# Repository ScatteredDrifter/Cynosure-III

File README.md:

# Cynosure-III
A 38-Key split-keyboard based on Xiao-rp2040 seeduino

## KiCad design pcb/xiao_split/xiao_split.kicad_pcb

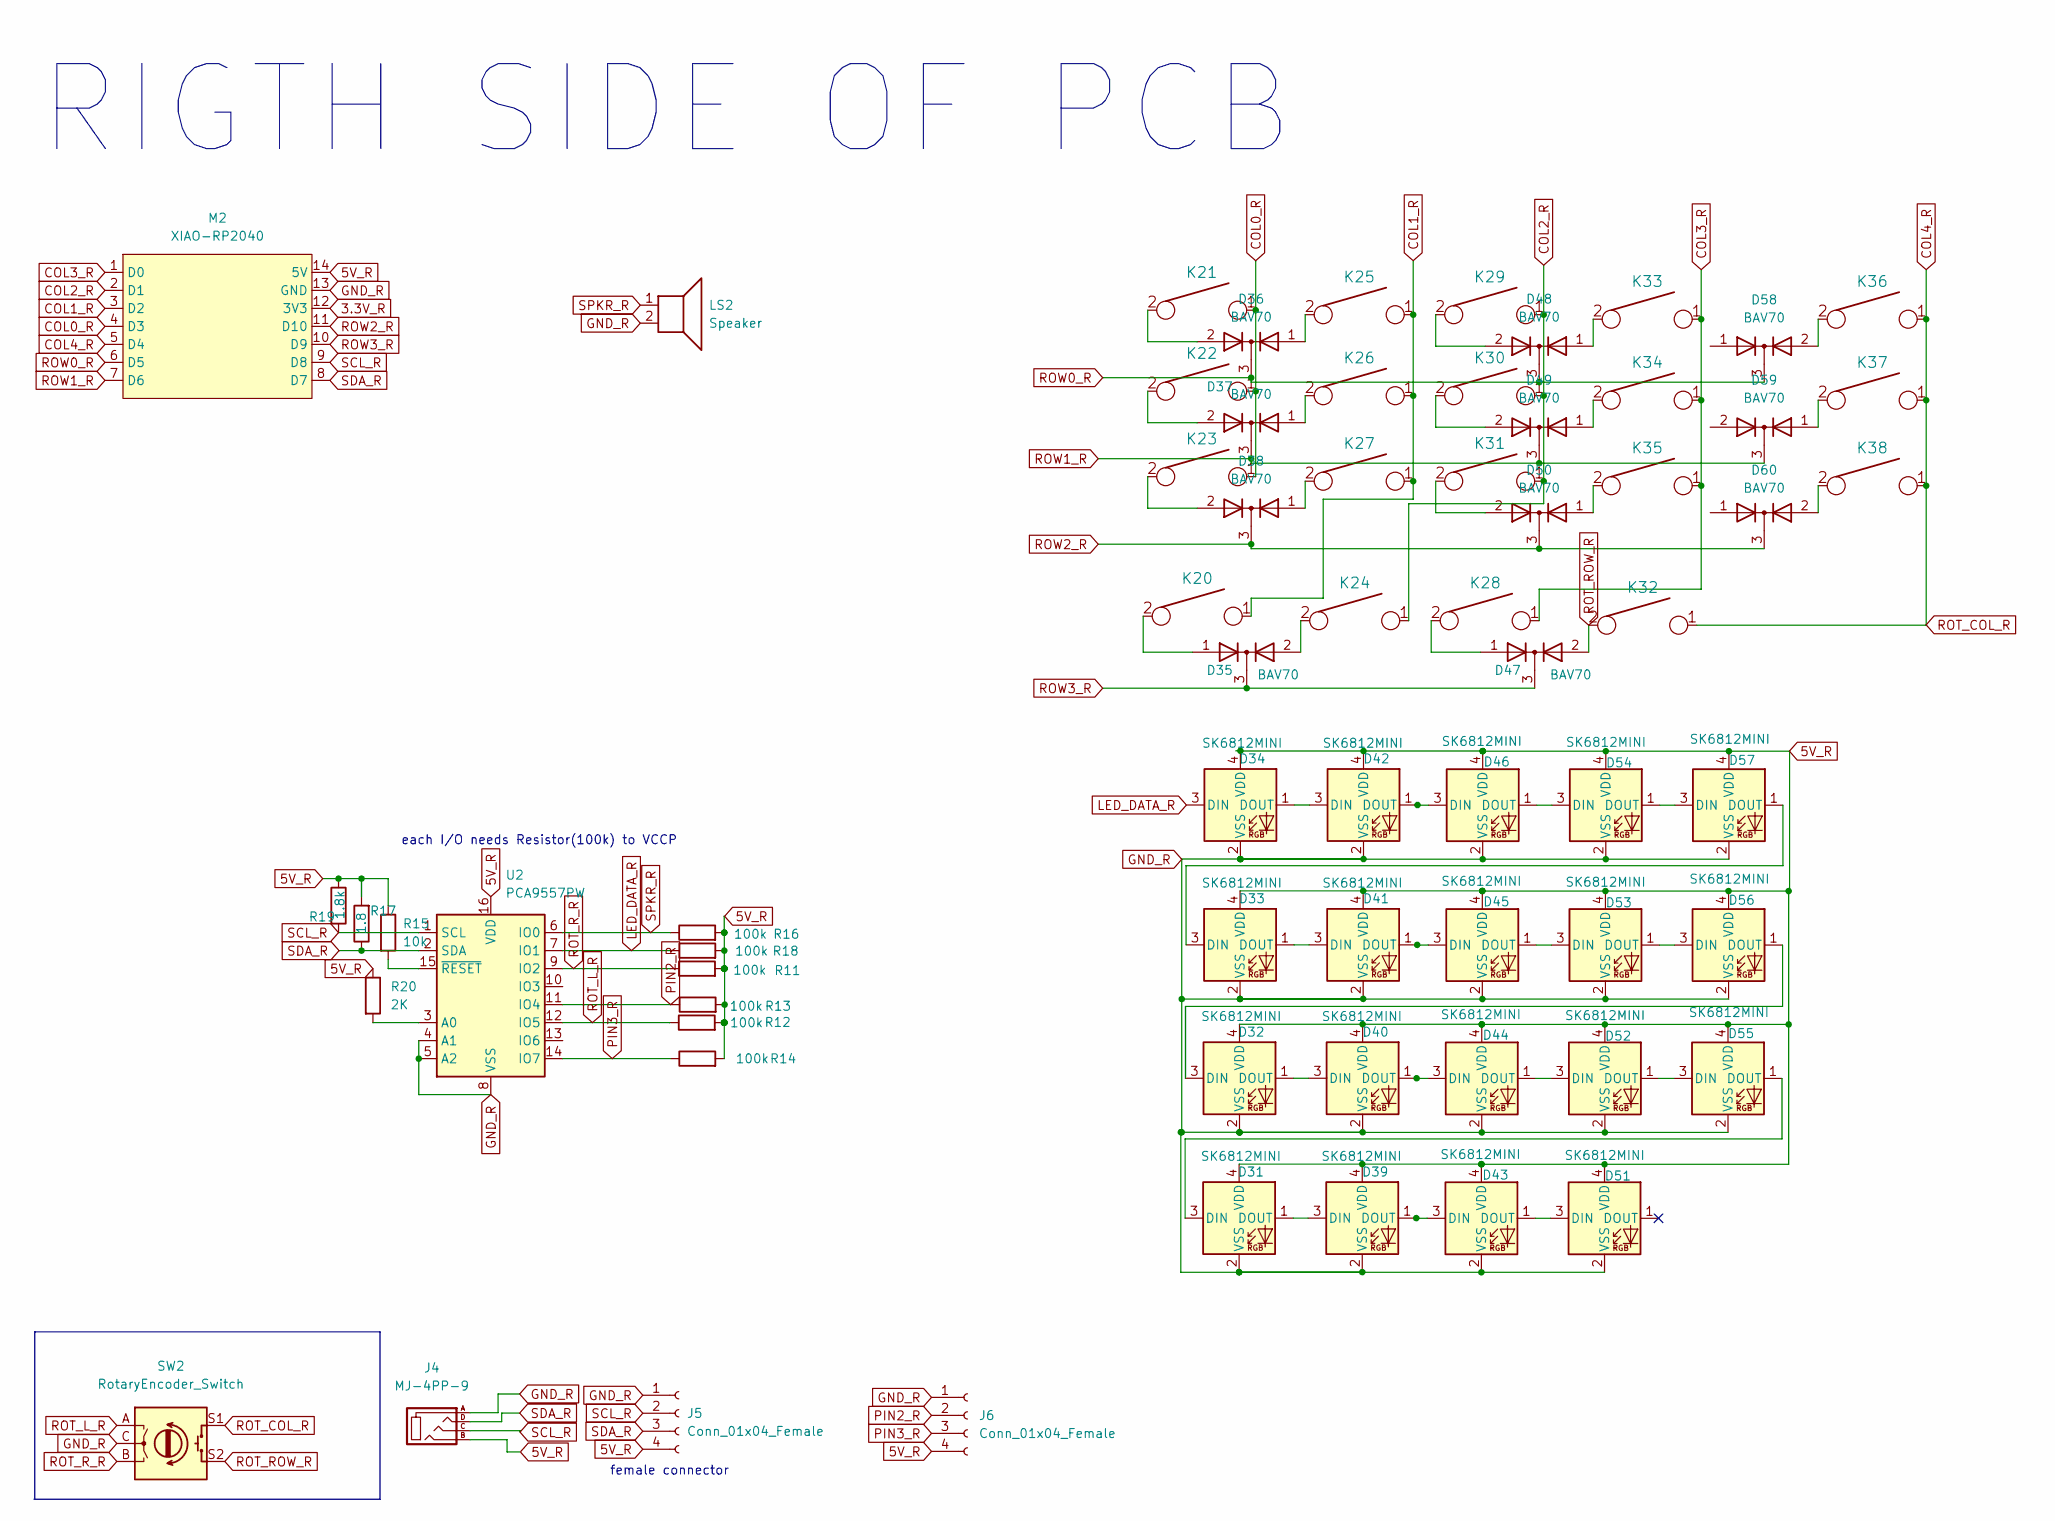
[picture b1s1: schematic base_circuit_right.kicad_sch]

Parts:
D31, D32, D33, D34, D39, D40, D41, D42, D43, D44, D45, D46, D51, D52, D53, D54, D55, D56, D57: SK6812MINI; SK6812-MINI-E; MPN SK6812MINI
D35, D36, D37, D38, D47, D48, D49, D50, D58, D59, D60: BAV70; SOT-23; MPN BAV70
J4: MJ-4PP-9; TRRS-PJ-320A; MPN PJ-3200B-4A
J5: Conn_01x04_Female; PinSocket_1x06_P2.54mm_Vertical
J6: Conn_01x04_Female; PinSocket_1x04_P2.00mm_Vertical
K20, K21, K22, K23, K24, K25, K26, K27, K28, K29, K30, K31, K32, K33, K34, K35, K36, K37, K38: KEYSW; MX-Alps-Choc-1U-NoLED; MPN 1350
LS2: Speaker; AST1109MLTRQ
M2: XIAO-RP2040; xiao-tht; MPN XIAO RP2040
R11, R12, R13, R14, R16, R18: 100k; R_0805_2012Metric; MPN RC0805FR-07100KL
R15: 10k; R_0805_2012Metric; MPN RC0805FR-0710KL
R17: 1.8; R_0805_2012Metric; MPN RC0805FR-071K8L
R19: 1.8k; R_0805_2012Metric; MPN RC0805FR-071K8L
R20: 2K; R_0805_2012Metric; MPN RC0805JR-072KL
SW2: RotaryEncoder_Switch; RotaryEncoder_EC11; MPN EC11E183440C
U2: PCA9557PW; TSSOP-16_4.4x5mm_P0.65mm

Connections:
3.3V_R: M2.12 (3V3)
5V_R: D31.4 (VDD), D32.4 (VDD), D33.4 (VDD), D34.4 (VDD), D39.4 (VDD), D40.4 (VDD), D41.4 (VDD), D42.4 (VDD), D43.4 (VDD), D44.4 (VDD), D45.4 (VDD), D46.4 (VDD), D51.4 (VDD), D52.4 (VDD), D53.4 (VDD), D54.4 (VDD), D55.4 (VDD), D56.4 (VDD), D57.4 (VDD), J4.B, J5.4, J6.4, M2.14 (5V), R11.2, R12.2, R13.2, R14.2, R15.1, R16.2, R17.2, R18.2, R19.1, R20.1, U2.16 (VDD)
COL0_R: K21.1, K22.1, K23.1, M2.4 (D3)
COL1_R: K20.1, K25.1, K26.1, K27.1, M2.3 (D2)
COL2_R: K24.1, K29.1, K30.1, K31.1, M2.2 (D1)
COL3_R: K28.1, K33.1, K34.1, K35.1, M2.1 (D0)
COL4_R: K32.1, K36.1, K37.1, K38.1, M2.5 (D4), SW2.S1
GND_R: D31.2 (VSS), D32.2 (VSS), D33.2 (VSS), D34.2 (VSS), D39.2 (VSS), D40.2 (VSS), D41.2 (VSS), D42.2 (VSS), D43.2 (VSS), D44.2 (VSS), D45.2 (VSS), D46.2 (VSS), D51.2 (VSS), D52.2 (VSS), D53.2 (VSS), D54.2 (VSS), D55.2 (VSS), D56.2 (VSS), D57.2 (VSS), J4.A, J5.1, J6.1, LS2.2, M2.13 (GND), SW2.C, U2.4 (A1), U2.5 (A2), U2.8 (VSS)
LED_DATA_R: D34.3 (DIN), R18.1, U2.7 (IO1)
unnamed: D31.1 (DOUT), D39.3 (DIN)
unnamed: D31.3 (DIN), D55.1 (DOUT)
unnamed: D32.1 (DOUT), D40.3 (DIN)
unnamed: D32.3 (DIN), D56.1 (DOUT)
unnamed: D33.1 (DOUT), D41.3 (DIN)
unnamed: D33.3 (DIN), D57.1 (DOUT)
unnamed: D34.1 (DOUT), D42.3 (DIN)
unnamed: D35.1 (A), K20.2
unnamed: D35.2 (A), K24.2
unnamed: D36.1 (A), K25.2
unnamed: D36.2 (A), K21.2
unnamed: D37.1 (A), K26.2
unnamed: D37.2 (A), K22.2
unnamed: D38.1 (A), K27.2
unnamed: D38.2 (A), K23.2
unnamed: D39.1 (DOUT), D43.3 (DIN)
unnamed: D40.1 (DOUT), D44.3 (DIN)
unnamed: D41.1 (DOUT), D45.3 (DIN)
unnamed: D42.1 (DOUT), D46.3 (DIN)
unnamed: D43.1 (DOUT), D51.3 (DIN)
unnamed: D44.1 (DOUT), D52.3 (DIN)
unnamed: D45.1 (DOUT), D53.3 (DIN)
unnamed: D46.1 (DOUT), D54.3 (DIN)
unnamed: D47.1 (A), K28.2
unnamed: D48.1 (A), K33.2
unnamed: D48.2 (A), K29.2
unnamed: D49.1 (A), K34.2
unnamed: D49.2 (A), K30.2
unnamed: D50.1 (A), K35.2
unnamed: D50.2 (A), K31.2
unnamed: D52.1 (DOUT), D55.3 (DIN)
unnamed: D53.1 (DOUT), D56.3 (DIN)
unnamed: D54.1 (DOUT), D57.3 (DIN)
unnamed: D58.2 (A), K36.2
unnamed: D59.1 (A), K37.2
unnamed: D60.2 (A), K38.2
unnamed: R20.2, U2.3 (A0)
unnamed: R15.2, U2.15 (~RESET)
PIN2_R: J6.2, R13.1, U2.11 (IO4)
PIN3_R: J6.3, R14.1, U2.14 (IO7)
ROT_L_R: R12.1, SW2.A, U2.12 (IO5)
ROT_ROW_R: D47.2 (A), K32.2, SW2.S2
ROT_R_R: R11.1, SW2.B, U2.9 (IO2)
ROW0_R: D36.3 (K), D48.3 (K), D58.3 (K), M2.6 (D5)
ROW1_R: D37.3 (K), D49.3 (K), D59.3 (K), M2.7 (D6)
ROW2_R: D38.3 (K), D50.3 (K), D60.3 (K), M2.11 (D10)
ROW3_R: D35.3 (K), D47.3 (K), M2.10 (D9)
SCL_R: J4.C, J5.2, M2.9 (D8), R19.2, U2.1 (SCL)
SDA_R: J4.D, J5.3, M2.8 (D7), R17.1, U2.2 (SDA)
SPKR_R: LS2.1, R16.1, U2.6 (IO0)

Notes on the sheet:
each I/O needs Resistor(100k) to VCCP
RIGTH SIDE OF PCB
female connector

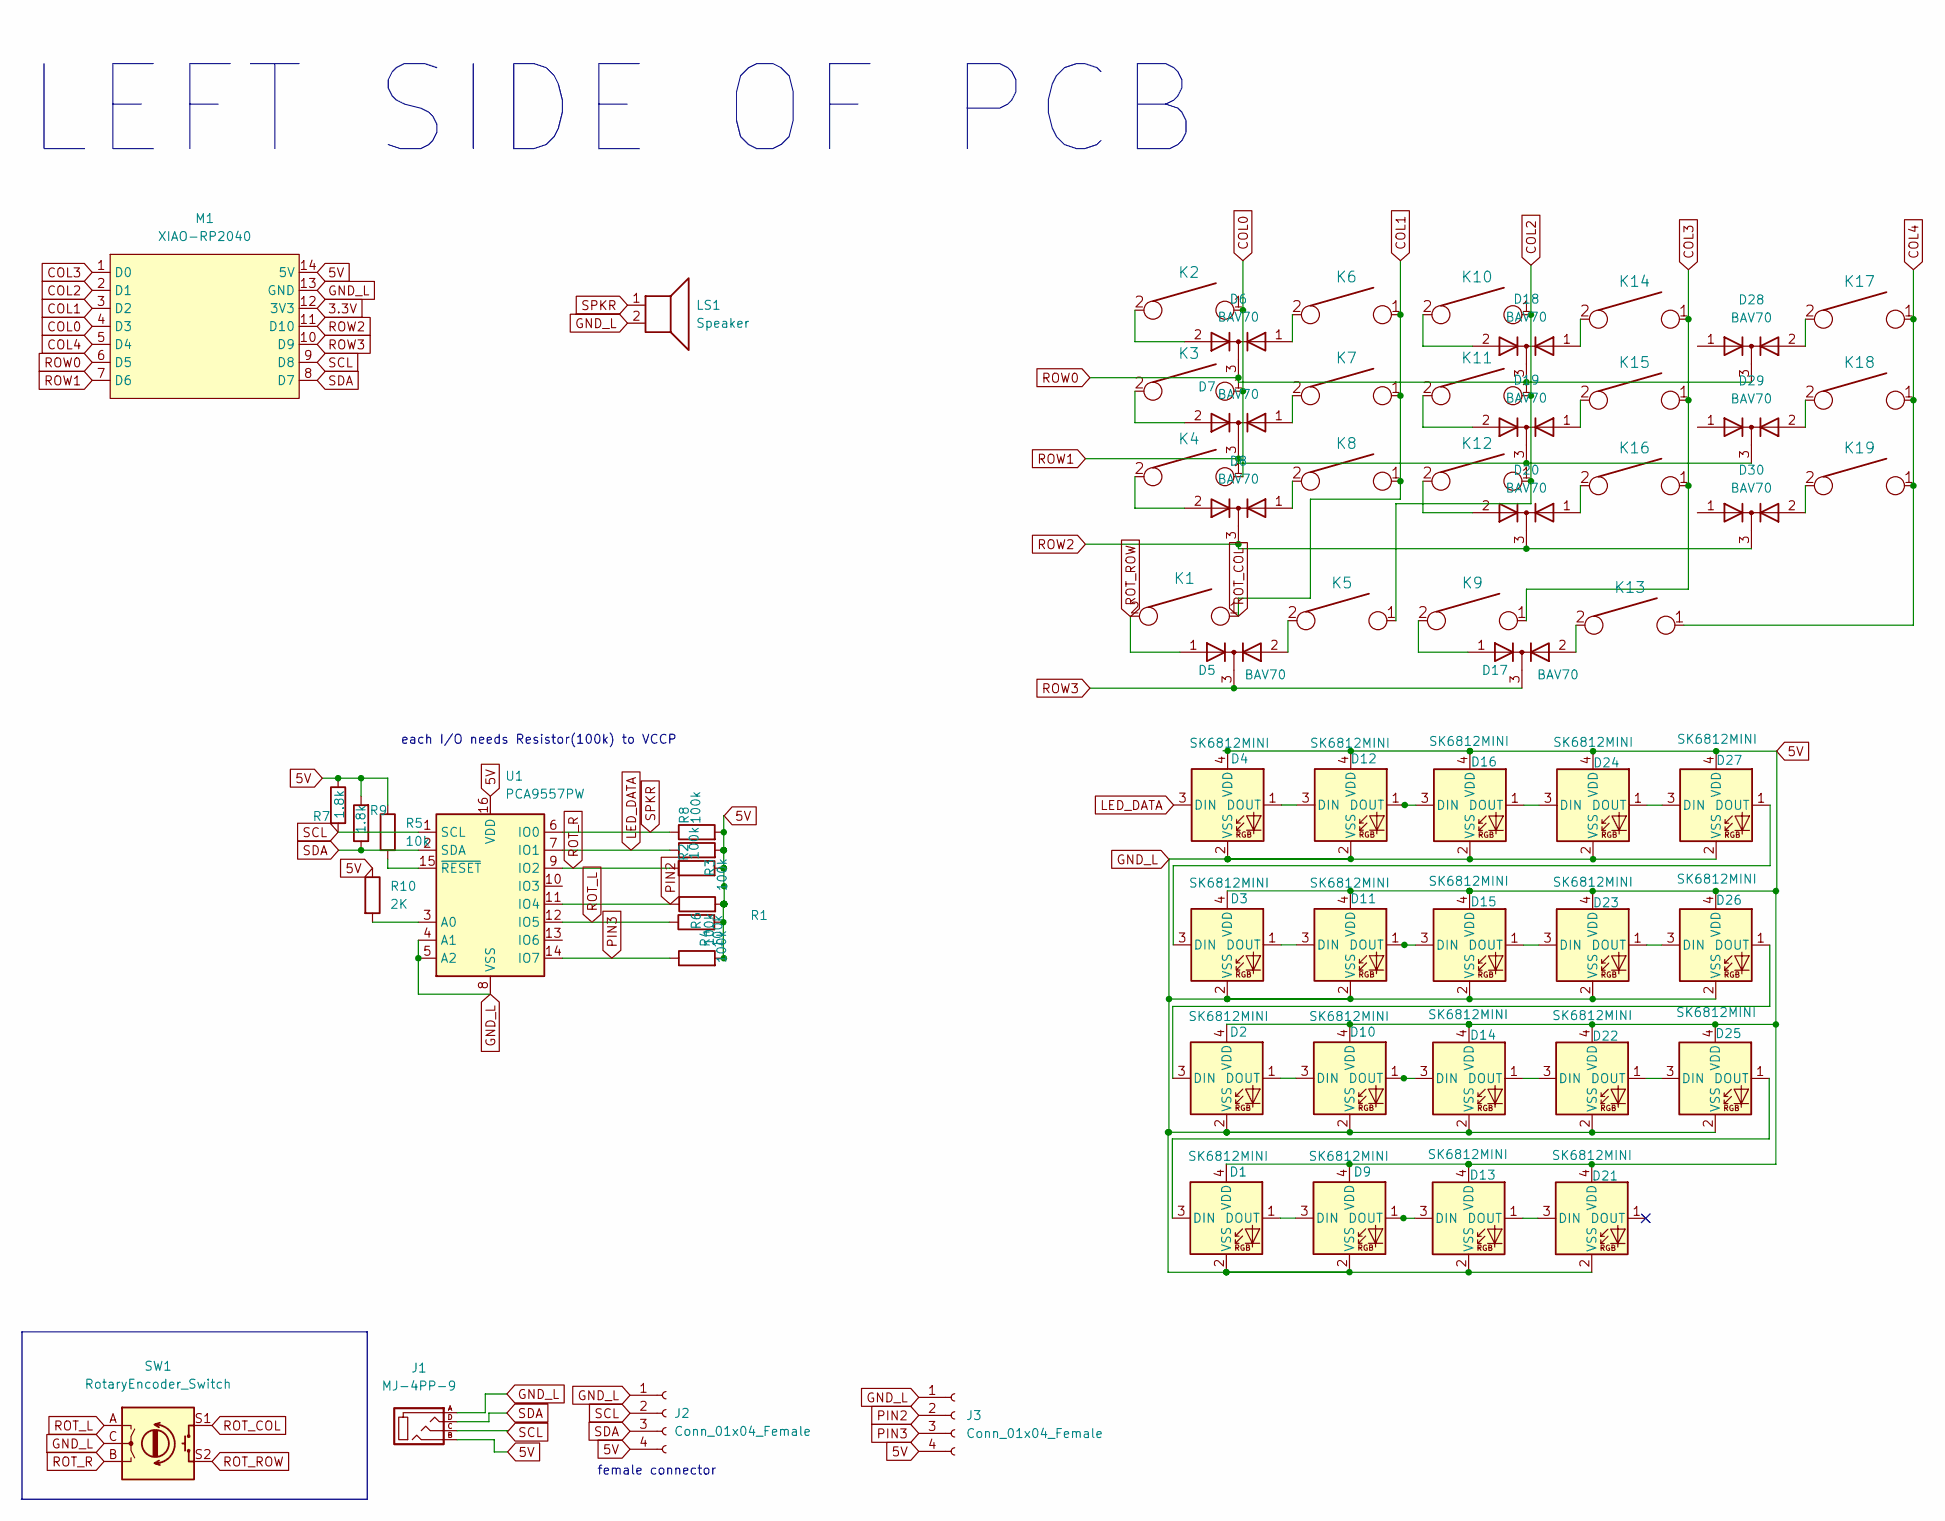
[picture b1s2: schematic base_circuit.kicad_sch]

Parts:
D1, D2, D3, D4, D9, D10, D11, D12, D13, D14, D15, D16, D21, D22, D23, D24, D25, D26, D27: SK6812MINI; SK6812-MINI-E; MPN SK6812MINI
D5, D6, D7, D8, D17, D18, D19, D20, D28, D29, D30: BAV70; SOT-23; MPN BAV70
J1: MJ-4PP-9; TRRS-PJ-320A; MPN PJ-3200B-4A
J2: Conn_01x04_Female; PinSocket_1x06_P2.54mm_Vertical
J3: Conn_01x04_Female; PinSocket_1x04_P2.00mm_Vertical
K1, K2, K3, K4, K5, K6, K7, K8, K9, K10, K11, K12, K13, K14, K15, K16, K17, K18, K19: KEYSW; MX-Alps-Choc-1U-NoLED; MPN 1350
LS1: Speaker; AST1109MLTRQ
M1: XIAO-RP2040; xiao-tht; MPN XIAO RP2040
R1, R2, R3, R4, R6, R8: 100k; R_0805_2012Metric; MPN RC0805FR-07100KL
R5: 10k; R_0805_2012Metric; MPN RC0805FR-0710KL
R7, R9: 1.8k; R_0805_2012Metric; MPN RC0805FR-071K8L
R10: 2K; R_0805_2012Metric; MPN RC0805JR-072KL
SW1: RotaryEncoder_Switch; RotaryEncoder_EC11; MPN EC11E183440C
U1: PCA9557PW; TSSOP-16_4.4x5mm_P0.65mm

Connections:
3.3V: M1.12 (3V3)
5V: D1.4 (VDD), D2.4 (VDD), D3.4 (VDD), D4.4 (VDD), D9.4 (VDD), D10.4 (VDD), D11.4 (VDD), D12.4 (VDD), D13.4 (VDD), D14.4 (VDD), D15.4 (VDD), D16.4 (VDD), D21.4 (VDD), D22.4 (VDD), D23.4 (VDD), D24.4 (VDD), D25.4 (VDD), D26.4 (VDD), D27.4 (VDD), J1.B, J2.4, J3.4, M1.14 (5V), R1.2, R4.2, R5.1, R6.2, R7.1, R8.2, R9.2, R10.1, U1.16 (VDD)
COL0: K2.1, K3.1, K4.1, M1.4 (D3)
COL1: K1.1, K6.1, K7.1, K8.1, M1.3 (D2), SW1.S1
COL2: K5.1, K10.1, K11.1, K12.1, M1.2 (D1)
COL3: K9.1, K14.1, K15.1, K16.1, M1.1 (D0)
COL4: K13.1, K17.1, K18.1, K19.1, M1.5 (D4)
GND_L: D1.2 (VSS), D2.2 (VSS), D3.2 (VSS), D4.2 (VSS), D9.2 (VSS), D10.2 (VSS), D11.2 (VSS), D12.2 (VSS), D13.2 (VSS), D14.2 (VSS), D15.2 (VSS), D16.2 (VSS), D21.2 (VSS), D22.2 (VSS), D23.2 (VSS), D24.2 (VSS), D25.2 (VSS), D26.2 (VSS), D27.2 (VSS), J1.A, J2.1, J3.1, LS1.2, M1.13 (GND), SW1.C, U1.4 (A1), U1.5 (A2), U1.8 (VSS)
LED_DATA: D4.3 (DIN), R3.1, U1.7 (IO1)
unnamed: D1.1 (DOUT), D9.3 (DIN)
unnamed: D1.3 (DIN), D25.1 (DOUT)
unnamed: D2.3 (DIN), D26.1 (DOUT)
unnamed: D5.2 (A), K5.2
unnamed: D6.1 (A), K6.2
unnamed: D6.2 (A), K2.2
unnamed: D7.1 (A), K7.2
unnamed: D7.2 (A), K3.2
unnamed: D8.1 (A), K8.2
unnamed: D8.2 (A), K4.2
unnamed: D10.1 (DOUT), D14.3 (DIN)
unnamed: D2.1 (DOUT), D10.3 (DIN)
unnamed: D11.1 (DOUT), D15.3 (DIN)
unnamed: D3.1 (DOUT), D11.3 (DIN)
unnamed: D12.1 (DOUT), D16.3 (DIN)
unnamed: D4.1 (DOUT), D12.3 (DIN)
unnamed: D13.1 (DOUT), D21.3 (DIN)
unnamed: D9.1 (DOUT), D13.3 (DIN)
unnamed: D14.1 (DOUT), D22.3 (DIN)
unnamed: D15.1 (DOUT), D23.3 (DIN)
unnamed: D16.1 (DOUT), D24.3 (DIN)
unnamed: D17.1 (A), K9.2
unnamed: D17.2 (A), K13.2
unnamed: D18.1 (A), K14.2
unnamed: D18.2 (A), K10.2
unnamed: D19.1 (A), K15.2
unnamed: D19.2 (A), K11.2
unnamed: D20.1 (A), K16.2
unnamed: D20.2 (A), K12.2
unnamed: D22.1 (DOUT), D25.3 (DIN)
unnamed: D23.1 (DOUT), D26.3 (DIN)
unnamed: D24.1 (DOUT), D27.3 (DIN)
unnamed: D3.3 (DIN), D27.1 (DOUT)
unnamed: D28.2 (A), K17.2
unnamed: D29.2 (A), K18.2
unnamed: D30.2 (A), K19.2
unnamed: R5.2, U1.15 (~RESET)
unnamed: R10.2, U1.3 (A0)
PIN2: J3.2, R6.1, U1.11 (IO4)
PIN3: J3.3, R4.1, U1.14 (IO7)
ROT_L: R1.1, SW1.A, U1.12 (IO5)
ROT_R: R2.1, SW1.B, U1.9 (IO2)
ROT_ROW: D5.1 (A), K1.2, SW1.S2
ROW0: D6.3 (K), D18.3 (K), D28.3 (K), M1.6 (D5)
ROW1: D7.3 (K), D19.3 (K), D29.3 (K), M1.7 (D6)
ROW2: D8.3 (K), D20.3 (K), D30.3 (K), M1.11 (D10)
ROW3: D5.3 (K), D17.3 (K), M1.10 (D9)
SCL: J1.C, J2.2, M1.9 (D8), R7.2, U1.1 (SCL)
SDA: J1.D, J2.3, M1.8 (D7), R9.1, U1.2 (SDA)
SPKR: LS1.1, R8.1, U1.6 (IO0)

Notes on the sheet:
each I/O needs Resistor(100k) to VCCP
LEFT SIDE OF PCB
female connector

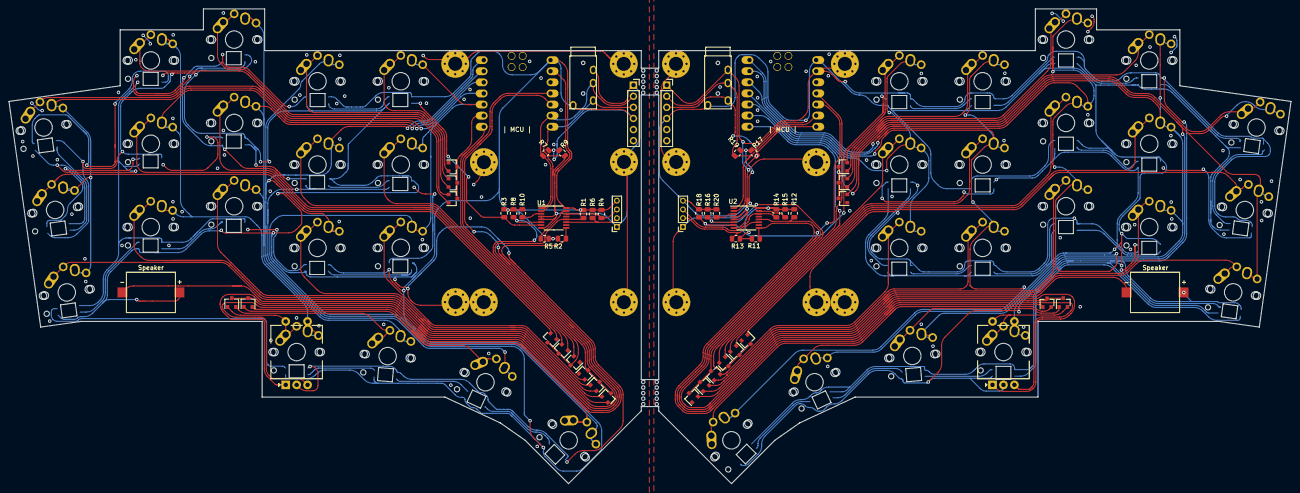
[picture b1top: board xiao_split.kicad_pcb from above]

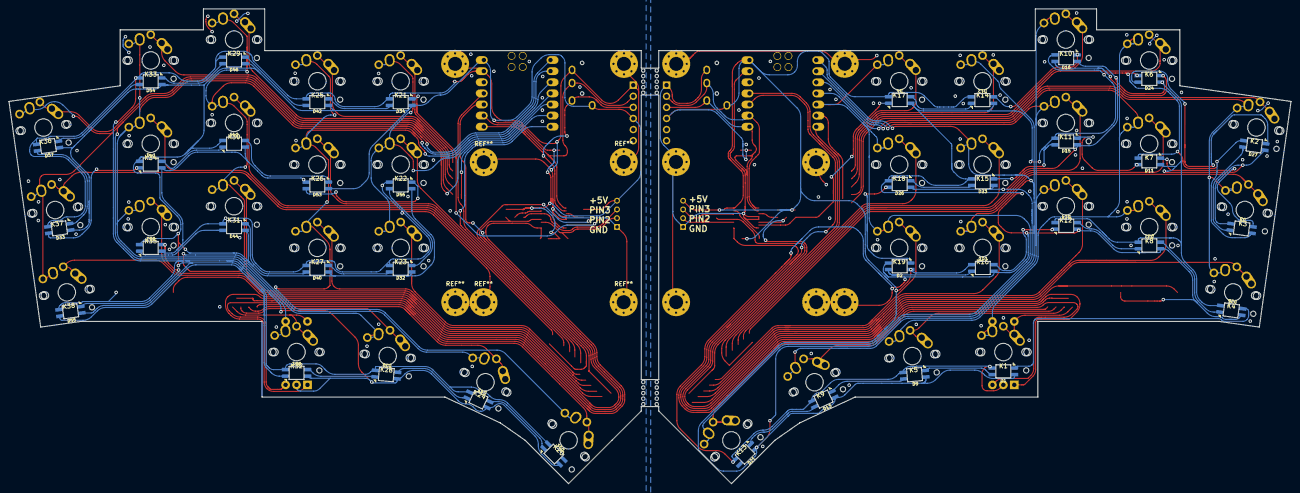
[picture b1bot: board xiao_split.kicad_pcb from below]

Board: 2 copper layers, 293.1 x 108.5 mm, 132 parts (38 on the bottom side), 116 nets.
